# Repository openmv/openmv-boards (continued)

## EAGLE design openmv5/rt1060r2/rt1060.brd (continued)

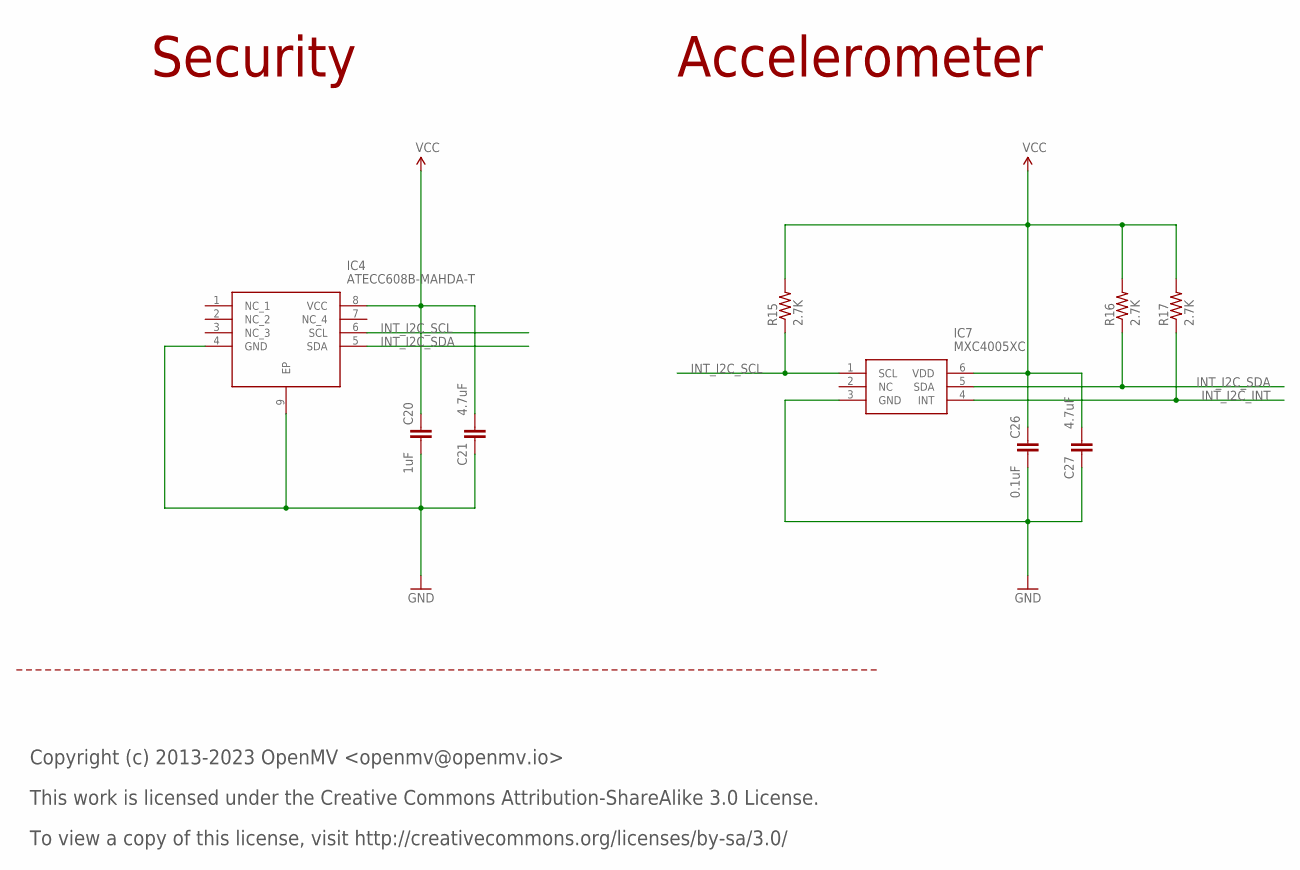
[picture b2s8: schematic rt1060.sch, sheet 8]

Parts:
C20: 1uF; 0402; MPN C0402C104Z4VAC
C21, C27: 4.7uF; 0402-CAP; MPN JMK105BBJ475MV-F
C26: 0.1uF; 0402; MPN C0402C104Z4VAC
IC4: ATECC608B-MAHDA-T; SON50P300X200X60-9N; MPN ATECC608B-MAHDA-T
IC7: MXC4005XC; MPN MXC4005XC
R15, R16, R17: 2.7K; 0402-RES; MPN AC0402JR-072K7L

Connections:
GND: C20.2, C21.1, C26.2, C27.1, IC4.4 (GND), IC4.9 (EP), IC7.3 (GND); also elsewhere on the board
INT_I2C_INT: IC7.4 (INT), R17.1; also elsewhere on the board
INT_I2C_SCL: IC4.6 (SCL), IC7.1 (SCL), R15.1; also elsewhere on the board
INT_I2C_SDA: IC4.5 (SDA), IC7.5 (SDA), R16.1; also elsewhere on the board
VCC: C20.1, C21.2, C26.1, C27.2, IC4.8 (VCC), IC7.6 (VDD), R15.2, R16.2, R17.2; also elsewhere on the board

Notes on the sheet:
Copyright (c) 2013-2023 OpenMV <openmv@openmv.io>
This work is licensed under the Creative Commons Attribution-ShareAlike 3.0 License.
To view a copy of this license, visit http://creativecommons.org/licenses/by-sa/3.0/
Security
Accelerometer

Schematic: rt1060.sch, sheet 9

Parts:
C35: 4.7uF; 0402-CAP; MPN JMK105BBJ475MV-F
C36: 0.1uF; 0402; MPN C0402C104Z4VAC
C37: 22uF; 0805; MPN CL21A226MQQNNNE
D6, D9: CPDQT5V0HE-HF; CPDQT5V0HEHF; MPN CPDQT5V0HE-HF
FL3: EMIF06-1005M12; SON40P150X250X65-13N; MPN EMIF06-1005M12
J5: USD-1040310811; 1040310811; MPN 104031-0811
R50, R51, R52, R53, R54, R55: 100K; 0402; MPN AC0402FR-07100KL

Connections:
GND: C35.1, C36.2, C37.2, D6.2, D9.2, FL3.13 (EP), J5.CD$2 (CD_POL), J5.G$1 (SHD), J5.G$2 (SHD), J5.G$3 (SHD), J5.G$4 (SHD), J5.P$6 (VSS); also elsewhere on the board
SD_CD: D9.1, J5.CD$1 (CD), R50.1; also elsewhere on the board
SD_CLK: FL3.4 (INPUT_4); also elsewhere on the board
SD_CLK_INT: FL3.9 (OUTPUT_4), J5.P$5 (CLK)
SD_CMD: FL3.3 (INPUT_3), R53.1; also elsewhere on the board
SD_CMD_INT: FL3.10 (OUTPUT_3), J5.P$3 (CMD)
SD_DAT0: FL3.5 (INPUT_5), R52.1; also elsewhere on the board
SD_DAT0_INT: FL3.8 (OUTPUT_5), J5.P$7 (DAT0)
SD_DAT1: FL3.6 (INPUT_6), R51.1; also elsewhere on the board
SD_DAT1_INT: FL3.7 (OUTPUT_6), J5.P$8 (DAT1)
SD_DAT2: FL3.1 (INPUT_1), R55.1; also elsewhere on the board
SD_DAT2_INT: FL3.12 (OUTPUT_1), J5.P$1 (DAT2)
SD_DAT3: FL3.2 (INPUT_2), R54.1; also elsewhere on the board
SD_DAT3_INT: FL3.11 (OUTPUT_2), J5.P$2 (DAT3/CD)
VCC: C35.2, C36.1, C37.1, D6.1, J5.P$4 (VDD), R50.2, R51.2, R52.2, R53.2, R54.2, R55.2; also elsewhere on the board

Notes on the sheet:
Copyright (c) 2013-2023 OpenMV <openmv@openmv.io>
This work is licensed under the Creative Commons Attribution-ShareAlike 3.0 License.
To view a copy of this license, visit http://creativecommons.org/licenses/by-sa/3.0/
SD CARD

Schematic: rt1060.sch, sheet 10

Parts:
C32, C51: 22uF; 0805; MPN CL21A226MQQNNNE
C33, C39, C40, C42, C44, C52: 4.7uF; 0402-CAP; MPN JMK105BBJ475MV-F
J4: DF12-36-DS; MPN DF12NB(3.0)-36DS-0.5V(51)
L4: 100; C0402; MPN MFBM1V1005-101-R
Q4, Q5: 2N7002KW_R1_00001; SOT65P210X110-3N; MPN 2N7002KW_R1_00001
R24, R25, R28: 100K; 0402-RES; MPN AC0402FR-07100KL
R26: 1K; 0402-RES; MPN CRCW04021K00FKEDC
R27, R29: 10K; 0402-RES; MPN AC0402FR-1310KL
R30, R31: 4.7K; 0402-RES; MPN AC0402FR-074K7L

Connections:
DCMI_CLK: J4.12; also elsewhere on the board
DCMI_D0: J4.31; also elsewhere on the board
DCMI_D1: J4.29; also elsewhere on the board
DCMI_D2: J4.35; also elsewhere on the board
DCMI_D3: J4.28; also elsewhere on the board
DCMI_D4: J4.26; also elsewhere on the board
DCMI_D5: J4.33; also elsewhere on the board
DCMI_D6: J4.24; also elsewhere on the board
DCMI_D7: J4.22; also elsewhere on the board
DCMI_FSIN: J4.23, Q5.3 (D), R28.1
DCMI_HSYNC: J4.18; also elsewhere on the board
DCMI_MISO: J4.15; also elsewhere on the board
DCMI_MOSI: J4.17; also elsewhere on the board
DCMI_PCLK: J4.14; also elsewhere on the board
DCMI_PWDN: J4.25, R29.1; also elsewhere on the board
DCMI_RST: J4.21, R27.1; also elsewhere on the board
DCMI_SCL: J4.32, R30.1; also elsewhere on the board
DCMI_SCLK: J4.13; also elsewhere on the board
DCMI_SDA: J4.34, R31.1; also elsewhere on the board
DCMI_SSEL: J4.11, R24.1; also elsewhere on the board
DCMI_VSYNC: J4.16; also elsewhere on the board
GND: C32.2, C33.1, C39.1, C40.1, C42.1, C44.1, C51.2, C52.1, J4.5, J4.19, J4.27, R27.2; also elsewhere on the board
P10_PWM: Q4.3 (D), R26.1; also elsewhere on the board
PWM_FSIN: Q4.2 (S), Q5.2 (S), R25.1; also elsewhere on the board
VCC: C32.1, C33.2, C39.2, C40.2, C42.2, C44.2, J4.2, J4.10, J4.20, J4.30, J4.36, L4.2, Q4.1 (G), Q5.1 (G), R24.2, R25.2, R26.2, R28.2, R29.2, R30.2, R31.2; also elsewhere on the board
VDDA: C51.1, C52.2, J4.4, L4.1

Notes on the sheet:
Copyright (c) 2013-2023 OpenMV <openmv@openmv.io>
This work is licensed under the Creative Commons Attribution-ShareAlike 3.0 License.
To view a copy of this license, visit http://creativecommons.org/licenses/by-sa/3.0/
IMAGE SENSOR CONNECTOR

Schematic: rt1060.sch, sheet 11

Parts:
D3: UHD1110-FKA-CL1A13R3Q1BBQFMF3; LED_UHD1110-FKA-CL1A13R3Q1BBQFMF3; MPN UHD1110-FKA-CL1A13r3q1BBQFMF3
D4, D5, D7, D8: CPDQT5V0HE-HF; CPDQT5V0HEHF; MPN CPDQT5V0HE-HF
FL2, FL4: EMIF06-1005M12; SON40P150X250X65-13N; MPN EMIF06-1005M12
J2, J3, J6: DNP; 1X08
R19, R20, R21: 220; 0402-RES; MPN CRGCQ0402F220R
R56, R57, R58: 10K; 0402; MPN AC0402FR-1310KL

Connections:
GND: D4.2, D5.2, D7.2, D8.2, FL2.13 (EP), FL4.13 (EP), J3.1, J6.1; also elsewhere on the board
LED_B: R19.1, R56.1; also elsewhere on the board
LED_B_INT: D3.1 (BLUE), R19.2
LED_G: R20.1, R57.1; also elsewhere on the board
LED_G_INT: D3.2 (GREEN), R20.2
LED_R: R21.1, R58.1; also elsewhere on the board
LED_R_INT: D3.3 (RED), R21.2
MDI_LED: J3.8; also elsewhere on the board
MDI_RX_N: J3.7; also elsewhere on the board
MDI_RX_P: J3.6; also elsewhere on the board
MDI_TX_N: J3.5; also elsewhere on the board
MDI_TX_P: J3.4; also elsewhere on the board
P0_MOSI: FL2.1 (INPUT_1); also elsewhere on the board
P0_MOSI_INT: FL2.12 (OUTPUT_1), J2.8
P1_MISO: FL2.2 (INPUT_2); also elsewhere on the board
P1_MISO_INT: FL2.11 (OUTPUT_2), J2.7
P2_SCLK: FL2.3 (INPUT_3); also elsewhere on the board
P2_SCLK_INT: FL2.10 (OUTPUT_3), J2.6
P3_NSS: FL2.4 (INPUT_4); also elsewhere on the board
P3_NSS_INT: FL2.9 (OUTPUT_4), J2.5
P4_SCL: FL2.5 (INPUT_5); also elsewhere on the board
P4_SCL_INT: FL2.8 (OUTPUT_5), J2.4
P5_SDA: FL2.6 (INPUT_6); also elsewhere on the board
P5_SDA_INT: FL2.7 (OUTPUT_6), J2.3
P6_ADC: FL4.1 (INPUT_1); also elsewhere on the board
P6_ADC_INT: FL4.12 (OUTPUT_1), J2.2
P7_PWM: FL4.2 (INPUT_2); also elsewhere on the board
P7_PWM_INT: FL4.11 (OUTPUT_2), J6.3
P8_PWM: FL4.3 (INPUT_3); also elsewhere on the board
P8_PWM_INT: FL4.10 (OUTPUT_3), J6.4
P9_PWM: FL4.4 (INPUT_4); also elsewhere on the board
P9_PWM_INT: FL4.9 (OUTPUT_4), J6.5
P10_PWM: FL4.5 (INPUT_5); also elsewhere on the board
P10_PWM_INT: FL4.8 (OUTPUT_5), J6.6
P11_WAKEUP: FL4.6 (INPUT_6); also elsewhere on the board
P11_WAKEUP_INT: FL4.7 (OUTPUT_6), J6.7
P12_RST_N_EXT: J6.8; also elsewhere on the board
PMIC_ONOFF: D8.1, J3.3; also elsewhere on the board
RAW: D5.1, J3.2; also elsewhere on the board
VCC: D3.4 (ANODE), D4.1, J2.1, R56.2, R57.2, R58.2; also elsewhere on the board
VIN: D7.1, J6.2; also elsewhere on the board

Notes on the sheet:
Copyright (c) 2013-2023 OpenMV <openmv@openmv.io>
This work is licensed under the Creative Commons Attribution-ShareAlike 3.0 License.
To view a copy of this license, visit http://creativecommons.org/licenses/by-sa/3.0/
I/O HEADERS
RGB LED

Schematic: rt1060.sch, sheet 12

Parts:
D10: CPDQT5V0HE-HF; CPDQT5V0HEHF; MPN CPDQT5V0HE-HF
FL5: EMIF06-1005M12; SON40P150X250X65-13N; MPN EMIF06-1005M12
J8: 3221-10-0300-00; CNC_3221-10-0300-00; MPN 3221-10-0300-00
R37: 10K; 0402-RES; MPN AC0402FR-1310KL

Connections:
BT_REG_ON: R37.1; also elsewhere on the board
GND: D10.2, FL5.13 (EP), J8.3, J8.5, R37.2; also elsewhere on the board
JTAG_TCK: FL5.4 (INPUT_4); also elsewhere on the board
JTAG_TCK_INT: FL5.9 (OUTPUT_4), J8.4
JTAG_TDI: FL5.2 (INPUT_2); also elsewhere on the board
JTAG_TDI_INT: FL5.11 (OUTPUT_2), J8.8
JTAG_TDO: FL5.3 (INPUT_3); also elsewhere on the board
JTAG_TDO_INT: FL5.10 (OUTPUT_3), J8.6
JTAG_TMS: FL5.5 (INPUT_5); also elsewhere on the board
JTAG_TMS_INT: FL5.8 (OUTPUT_5), J8.2
JTAG_TRSTB: FL5.6 (INPUT_6); also elsewhere on the board
JTAG_TRSTB_INT: FL5.7 (OUTPUT_6), J8.9
P12_RST_N: FL5.1 (INPUT_1); also elsewhere on the board
P12_RST_N_EXT: FL5.12 (OUTPUT_1), J8.10; also elsewhere on the board
VCC: D10.1, J8.1; also elsewhere on the board

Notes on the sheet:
Copyright (c) 2013-2023 OpenMV <openmv@openmv.io>
This work is licensed under the Creative Commons Attribution-ShareAlike 3.0 License.
To view a copy of this license, visit http://creativecommons.org/licenses/by-sa/3.0/
JTAG

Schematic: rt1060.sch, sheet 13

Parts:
C65, C81, C83, C90: 4.7uF; 0402-CAP; MPN JMK105BBJ475MV-F
C82, C84, C89: 0.1uF; 0402; MPN C0402C104Z4VAC
C85, C96: 22uF; 0805; MPN CL21A226MQQNNNE
FD1, FD2, FD3, FD4, FD5, FD6, FD7, FD8: FIDUCIAL1X2; FIDUCIAL-1X2
H1, H2: MOUNT-PAD-ROUND2.8; 2,8-PAD
IC9: KSZ8081RNDCA-TR; QFN50P400X400X90-25N; MPN KSZ8081RNDCA-TR
L8: 100; C0402; MPN MFBM1V1005-101-R
M1, M2: 9774030151R; MPN 9774030151R
R34: 100K; 0402-RES; MPN AC0402FR-07100KL
R35: 220; 0402-RES; MPN CRGCQ0402F220R
R36, R39: 1K; 0402-RES; MPN CRCW04021K00FKEDC
R38: 6.49K; 0402-RES; MPN CR0402-FX-6491GLF

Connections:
ETH_INT: IC9.18 (INTRP), R36.1; also elsewhere on the board
ETH_LED: IC9.23 (LED0_/_ANEN_SPEED), R35.1
ETH_MDC: IC9.11 (MDC); also elsewhere on the board
ETH_MDIO: IC9.10 (MDIO), R39.1; also elsewhere on the board
ETH_RST: C65.2, IC9.24 (RST#), R34.1; also elsewhere on the board
ETH_RXD0: IC9.13 (RXD0); also elsewhere on the board
ETH_RXD1: IC9.12 (RXD1); also elsewhere on the board
ETH_RXDV: IC9.15 (CRS_DV/_PHYAD[1:0]); also elsewhere on the board
ETH_RXERR: IC9.17 (RXER); also elsewhere on the board
ETH_TXCLK: IC9.8 (XI); also elsewhere on the board
ETH_TXD0: IC9.20 (TXD0); also elsewhere on the board
ETH_TXD1: IC9.21 (TXD1); also elsewhere on the board
ETH_TXEN: IC9.19 (TXEN); also elsewhere on the board
ETH_VDDA_3.3: C81.2, C82.1, C85.1, IC9.2 (VDDA_3.3), L8.1
ETH_VDD_1.2: C83.2, C84.1, IC9.1 (VDD_1.2)
GND: C65.1, C81.1, C82.2, C83.1, C84.2, C85.2, C89.2, C90.1, C96.2, IC9.22 (GND_1), IC9.25 (GND_2), R38.2; also elsewhere on the board
MDI_LED: R35.2; also elsewhere on the board
MDI_RX_N: IC9.3 (RXM); also elsewhere on the board
MDI_RX_P: IC9.4 (RXP); also elsewhere on the board
MDI_TX_N: IC9.5 (TXM); also elsewhere on the board
MDI_TX_P: IC9.6 (TXP); also elsewhere on the board
REXT: IC9.9 (REXT), R38.1
VCC: C89.1, C90.2, C96.1, IC9.14 (VDDIO), L8.2, R34.2, R36.2, R39.2; also elsewhere on the board

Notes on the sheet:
Copyright (c) 2013-2023 OpenMV <openmv@openmv.io>
This work is licensed under the Creative Commons Attribution-ShareAlike 3.0 License.
To view a copy of this license, visit http://creativecommons.org/licenses/by-sa/3.0/
Ethernet
Mechanical

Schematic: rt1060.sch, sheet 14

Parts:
ANT1: AMCA31-2R450G-S1F-T3; ANTC3216X140N; MPN AMCA31-2R450G-S1F-T3
C74, C75, C76, C111: 0.1uF; 0402; MPN C0402C104Z4VAC
C77: GRM0335C1H1R5BA01D; CAPC0603X33N; MPN GRM0335C1H1R5BA01D
C78: DNP; CAPC0603X33N; MPN GRM0335C1H1R5BA01D
C91, C92, C93: 4.7uF; 0402-CAP; MPN JMK105BBJ475MV-F
J7: DNP; 23370191; MPN 2337019-1
L7: 3.9NH; 0402; MPN L-07C3N9SV6T
L9: MAKK2016T2R2M; INDC2016X100N; MPN MAKK2016T2R2M
R43, R44: 10K; 0402; MPN AC0402FR-1310KL
R45, R46, R47, R48, R49: 100K; 0402; MPN AC0402FR-07100KL
U3: LBEE5KL1DX-883; XCVR_LBEE5KL1DX-TEMP; MPN LBEE5KL1DX-883
Y3: ECS-327MVATX-3-CN-TR3; ECS327MVATX3CNTR3; MPN ECS-327MVATX-3-CN-TR3

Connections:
ANT: C77.1, J7.1 (SIGNAL), L7.2, U3.41 (ANT)
BT_D_WAKE: U3.39 (BT_DEV_WAKE); also elsewhere on the board
BT_H_WAKE: R44.1, U3.38 (BT_HOST_WAKE); also elsewhere on the board
BT_REG_ON: U3.14 (BT_REG_ON); also elsewhere on the board
BT_UART_CTS: U3.5 (!BT_UART_RTS_N); also elsewhere on the board
BT_UART_RTS: U3.4 (!BT_UART_CTS_N); also elsewhere on the board
BT_UART_RX: U3.3 (BT_UART_TXD); also elsewhere on the board
BT_UART_TX: U3.2 (BT_UART_RXD); also elsewhere on the board
FEED: ANT1.1 (FEED), C78.1, L7.1
GND: C74.2, C75.2, C76.2, C77.2, C78.2, C91.1, C92.1, C93.1, C111.2, J7.2 (GND_1), J7.3 (GND_2), U3.1 (GND), U3.12 (GND), U3.19 (GND), U3.21 (GND), U3.29 (GND), U3.32 (GND_(SR_PVSS)), U3.33 (GND_(SR_PVSS)), U3.35 (GND), U3.40 (GND), U3.42 (GND), U3.43 (GND), U3.44 (GND), U3.45 (GND), U3.46 (GND), Y3.2 (GND); also elsewhere on the board
LPO_IN: U3.37 (LPO_IN_(32KHZ)), Y3.3 (OUTPUT)
SR_VLX: L9.1, U3.34 (SR_VLX)
VCC: C75.1, C76.1, C92.2, C93.2, C111.1, R43.2, R44.2, R45.2, R46.2, R47.2, R48.2, R49.2, U3.30 (VBAT), U3.36 (VIO), Y3.1 (TRI-STATE), Y3.4 (VDD); also elsewhere on the board
VIN_LDO: C74.1, C91.2, L9.2, U3.31 (VIN_LDO)
WIFI_CLK: U3.20 (SDIO_CLK); also elsewhere on the board
WIFI_CMD: R49.1, U3.22 (SDIO_CMD); also elsewhere on the board
WIFI_D0: R48.1, U3.24 (SDIO_DATA_0); also elsewhere on the board
WIFI_D1: R47.1, U3.26 (SDIO_DATA_1); also elsewhere on the board
WIFI_D2: R46.1, U3.23 (SDIO_DATA_2); also elsewhere on the board
WIFI_D3: R45.1, U3.25 (SDIO_DATA_3); also elsewhere on the board
WL_H_WAKE: R43.1, U3.27 (WL_GPIO_0_HOST_WAKE); also elsewhere on the board
WL_REG_ON: U3.28 (WL_REG_ON); also elsewhere on the board

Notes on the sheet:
Copyright (c) 2013-2023 OpenMV <openmv@openmv.io>
This work is licensed under the Creative Commons Attribution-ShareAlike 3.0 License.
To view a copy of this license, visit http://creativecommons.org/licenses/by-sa/3.0/
WiFi/Bluetooth

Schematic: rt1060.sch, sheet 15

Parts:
C34, C38, C43, C45, C47, C48, C50, C53, C54, C55, C56, C59, C62, C63, C66, C68, C69, C70, C71, C86, C87, C88, C94, C97, C98, C99, C100, C102, C103, C107, C109: 0.22uF; C0201; MPN GRM033R60J224ME15D
C41, C46, C57, C60, C64, C67, C72, C95, C101, C104, C108: 4.7uF; 0402-CAP; MPN JMK105BBJ475MV-F
C49, C58, C61, C73: 22uF; 0805; MPN CL21A226MQQNNNE
C79, C80: 18pF; C0201; MPN GRM0335C1E180JA01D
C105, C106: 4.7pF; C0201; MPN GRM0335C1E4R7CA01D
IC8: MIMXRT1052DVL6B; BGA196C65P14X14_1000X1000X143; MPN MIMXRT1052DVL6B
L5: MAKK2016T4R7M; INDC2016X100N; MPN MAKK2016T4R7M
L6: 100; C0402; MPN MFBM1V1005-101-R
R32: 30K; 0402-RES; MPN 0402WGF3002TCE
R33, R42: 10K; 0402-RES; MPN AC0402FR-1310KL
R40: 2.2M; 0402-RES; MPN RC0402FR-072M2L
S1: KMS231GLFS; MPN KMS231GLFS
Y1: SC32S-7PF20PPM; XTAL_ABS07-32.768KHZ-7-T; MPN SC32S-7PF20PPM
Y2: XRCGB24M000F3M00R0; MPN XRCGB24M000F3M00R0

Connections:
BT_D_WAKE: IC8.L5 (GPIO_SD_B1_00); also elsewhere on the board
BT_H_WAKE: IC8.H14 (GPIO_AD_B0_14); also elsewhere on the board
BT_REG_ON: IC8.F13 (GPIO_AD_B0_08); also elsewhere on the board
BT_UART_CTS: IC8.L12 (GPIO_AD_B1_04); also elsewhere on the board
BT_UART_RTS: IC8.K12 (GPIO_AD_B1_05); also elsewhere on the board
BT_UART_RX: IC8.C9 (GPIO_B0_09); also elsewhere on the board
BT_UART_TX: IC8.B9 (GPIO_B0_08); also elsewhere on the board
DCDC_LP: IC8.M1 (DCDC_LP_1), IC8.M2 (DCDC_LP_2), L5.2
DCDC_PSWITCH: C62.1, IC8.K3 (DCDC_PSWITCH), R32.1
DCMI_CLK: IC8.B14 (GPIO_B1_15); also elsewhere on the board
DCMI_D0: IC8.J14 (GPIO_AD_B1_15); also elsewhere on the board
DCMI_D1: IC8.G12 (GPIO_AD_B1_14); also elsewhere on the board
DCMI_D2: IC8.H11 (GPIO_AD_B1_13); also elsewhere on the board
DCMI_D3: IC8.H12 (GPIO_AD_B1_12); also elsewhere on the board
DCMI_D4: IC8.J13 (GPIO_AD_B1_11); also elsewhere on the board
DCMI_D5: IC8.L13 (GPIO_AD_B1_10); also elsewhere on the board
DCMI_D6: IC8.G14 (GPIO_AD_B0_05); also elsewhere on the board
DCMI_D7: IC8.F11 (GPIO_AD_B0_04), S1.1 (NO_1), S1.5 (NO_2); also elsewhere on the board
DCMI_HSYNC: IC8.L10 (GPIO_AD_B0_15); also elsewhere on the board
DCMI_MISO: IC8.E7 (GPIO_B0_01); also elsewhere on the board
DCMI_MOSI: IC8.E8 (GPIO_B0_02); also elsewhere on the board
DCMI_PCLK: IC8.D13 (GPIO_B1_12); also elsewhere on the board
DCMI_PWDN: IC8.C11 (GPIO_B1_02); also elsewhere on the board
DCMI_RST: IC8.B11 (GPIO_B1_01); also elsewhere on the board
DCMI_SCL: IC8.J11 (GPIO_AD_B1_00); also elsewhere on the board
DCMI_SCLK: IC8.D8 (GPIO_B0_03); also elsewhere on the board
DCMI_SDA: IC8.K11 (GPIO_AD_B1_01); also elsewhere on the board
DCMI_SSEL: IC8.D7 (GPIO_B0_00); also elsewhere on the board
DCMI_VSYNC: IC8.D14 (GPIO_B1_13); also elsewhere on the board
ETH_INT: IC8.C10 (GPIO_B0_12); also elsewhere on the board
ETH_MDC: IC8.A7 (GPIO_EMC_40); also elsewhere on the board
ETH_MDIO: IC8.C7 (GPIO_EMC_41); also elsewhere on the board
ETH_RST: IC8.D10 (GPIO_B0_13); also elsewhere on the board
ETH_RXD0: IC8.E12 (GPIO_B1_04); also elsewhere on the board
ETH_RXD1: IC8.D12 (GPIO_B1_05); also elsewhere on the board
ETH_RXDV: IC8.C12 (GPIO_B1_06); also elsewhere on the board
ETH_RXERR: IC8.C13 (GPIO_B1_11); also elsewhere on the board
ETH_TXCLK: IC8.B13 (GPIO_B1_10); also elsewhere on the board
ETH_TXD0: IC8.B12 (GPIO_B1_07); also elsewhere on the board
ETH_TXD1: IC8.A12 (GPIO_B1_08); also elsewhere on the board
ETH_TXEN: IC8.A13 (GPIO_B1_09); also elsewhere on the board
GND: C34.2, C38.2, C41.1, C43.2, C45.2, C46.1, C47.2, C48.2, C49.1, C50.2, C53.2, C54.2, C55.2, C56.2, C57.1, C58.1, C59.2, C60.1, C61.1, C62.2, C63.2, C64.2, C66.1, C67.2, C68.1, C69.2, C70.2, C71.2, C72.1, C73.1, C79.2, C80.2, C86.1, C87.1, C88.2, C94.1, C95.1, C97.1, C98.1, C99.1, C100.1, C101.1, C102.2, C103.1, C104.1, C105.2, C106.2, C107.2, C108.1, C109.2, IC8.A1 (VSS_1), IC8.A14 (VSS_2), IC8.B5 (VSS_3), IC8.B10 (VSS_4), IC8.E2 (VSS_5), IC8.E13 (VSS_6), IC8.G7 (VSS_7), IC8.G8 (VSS_8), IC8.H7 (VSS_9), IC8.H8 (VSS_10), IC8.J7 (VSS_11), IC8.J8 (VSS_12), IC8.K2 (VSS_13), IC8.K6 (TEST_MODE), IC8.K9 (NGND_KEL0), IC8.K13 (VSS_14), IC8.L9 (VSS_15), IC8.N1 (DCDC_GND_1), IC8.N2 (DCDC_GND_2), IC8.N5 (VSS_16), IC8.N8 (VSS_17), IC8.P1 (VSS_18), IC8.P14 (VSS_19), R40.2, Y2.2 (NC_1), Y2.4 (NC_2); also elsewhere on the board
INT_I2C_INT: IC8.D11 (GPIO_B1_03); also elsewhere on the board
INT_I2C_SCL: IC8.C8 (GPIO_B0_04); also elsewhere on the board
INT_I2C_SDA: IC8.B8 (GPIO_B0_05); also elsewhere on the board
JTAG_TCK: IC8.F12 (GPIO_AD_B0_07); also elsewhere on the board
JTAG_TDI: IC8.F14 (GPIO_AD_B0_09); also elsewhere on the board
JTAG_TDO: IC8.G13 (GPIO_AD_B0_10); also elsewhere on the board
JTAG_TMS: IC8.E14 (GPIO_AD_B0_06); also elsewhere on the board
JTAG_TRSTB: IC8.G10 (GPIO_AD_B0_11); also elsewhere on the board
LED_B: IC8.C14 (GPIO_B1_14); also elsewhere on the board
LED_G: IC8.A10 (GPIO_B0_11); also elsewhere on the board
LED_R: IC8.D9 (GPIO_B0_10); also elsewhere on the board
NVCC_PLL: C104.2, C107.1, IC8.P10 (NVCC_PLL)
ONOFF: IC8.M6 (ONOFF); also elsewhere on the board
ON_BATTERY: IC8.P2 (GPIO_SD_B1_04); also elsewhere on the board
P0_MOSI: IC8.H10 (GPIO_AD_B0_01); also elsewhere on the board
P1_MISO: IC8.M11 (GPIO_AD_B0_02); also elsewhere on the board
P2_SCLK: IC8.M14 (GPIO_AD_B0_00); also elsewhere on the board
P3_NSS: IC8.G11 (GPIO_AD_B0_03); also elsewhere on the board
P4_SCL: IC8.K14 (GPIO_AD_B0_12); also elsewhere on the board
P5_SDA: IC8.L14 (GPIO_AD_B0_13); also elsewhere on the board
P6_ADC: IC8.M12 (GPIO_AD_B1_03); also elsewhere on the board
P7_PWM: IC8.A8 (GPIO_B0_06); also elsewhere on the board
P8_PWM: IC8.A9 (GPIO_B0_07); also elsewhere on the board
P9_PWM: IC8.A11 (GPIO_B1_00); also elsewhere on the board
P12_RST_N: C63.1, IC8.M7 (POR_B), R33.2; also elsewhere on the board
PMIC_ON_REQ: IC8.K7 (PMIC_ON_REQ); also elsewhere on the board
PWM_FSIN: IC8.M5 (GPIO_SD_B1_01); also elsewhere on the board
P_FLASH_CE: IC8.L3 (GPIO_SD_B1_06); also elsewhere on the board
P_FLASH_IO0: IC8.P3 (GPIO_SD_B1_08); also elsewhere on the board
P_FLASH_IO1: IC8.N4 (GPIO_SD_B1_09); also elsewhere on the board
P_FLASH_IO2: IC8.P4 (GPIO_SD_B1_10); also elsewhere on the board
P_FLASH_IO3: IC8.P5 (GPIO_SD_B1_11); also elsewhere on the board
P_FLASH_SCK: IC8.L4 (GPIO_SD_B1_07); also elsewhere on the board
RTC_XTALI: C80.1, IC8.N9 (RTC_XTALI), Y1.2
RTC_XTALO: C79.1, IC8.P9 (RTC_XTALO), Y1.1
SBL_BOOT: R42.2, S1.2 (COM_1), S1.3 (COM_2), S1.4 (COM_3)
SDRAM_A0: IC8.C2 (GPIO_EMC_09); also elsewhere on the board
SDRAM_A1: IC8.G1 (GPIO_EMC_10); also elsewhere on the board
SDRAM_A2: IC8.G3 (GPIO_EMC_11); also elsewhere on the board
SDRAM_A3: IC8.H1 (GPIO_EMC_12); also elsewhere on the board
SDRAM_A4: IC8.A6 (GPIO_EMC_13); also elsewhere on the board
SDRAM_A5: IC8.B6 (GPIO_EMC_14); also elsewhere on the board
SDRAM_A6: IC8.B1 (GPIO_EMC_15); also elsewhere on the board
SDRAM_A7: IC8.A5 (GPIO_EMC_16); also elsewhere on the board
SDRAM_A8: IC8.A4 (GPIO_EMC_17); also elsewhere on the board
SDRAM_A9: IC8.B2 (GPIO_EMC_18); also elsewhere on the board
SDRAM_A10: IC8.G2 (GPIO_EMC_23); also elsewhere on the board
SDRAM_A11: IC8.B4 (GPIO_EMC_19); also elsewhere on the board
SDRAM_A12: IC8.A3 (GPIO_EMC_20); also elsewhere on the board
SDRAM_BA0: IC8.C1 (GPIO_EMC_21); also elsewhere on the board
SDRAM_BA1: IC8.F1 (GPIO_EMC_22); also elsewhere on the board
SDRAM_CAS: IC8.D3 (GPIO_EMC_24); also elsewhere on the board
SDRAM_CKE: IC8.A2 (GPIO_EMC_27); also elsewhere on the board
SDRAM_CLK: IC8.B3 (GPIO_EMC_26); also elsewhere on the board
SDRAM_CS: IC8.E1 (GPIO_EMC_29); also elsewhere on the board
SDRAM_DQ0: IC8.E3 (GPIO_EMC_00); also elsewhere on the board
SDRAM_DQ1: IC8.F3 (GPIO_EMC_01); also elsewhere on the board
SDRAM_DQ2: IC8.F4 (GPIO_EMC_02); also elsewhere on the board
SDRAM_DQ3: IC8.G4 (GPIO_EMC_03); also elsewhere on the board
SDRAM_DQ4: IC8.F2 (GPIO_EMC_04); also elsewhere on the board
SDRAM_DQ5: IC8.G5 (GPIO_EMC_05); also elsewhere on the board
SDRAM_DQ6: IC8.H5 (GPIO_EMC_06); also elsewhere on the board
SDRAM_DQ7: IC8.H4 (GPIO_EMC_07); also elsewhere on the board
SDRAM_DQ8: IC8.C6 (GPIO_EMC_30); also elsewhere on the board
SDRAM_DQ9: IC8.C5 (GPIO_EMC_31); also elsewhere on the board
SDRAM_DQ10: IC8.D5 (GPIO_EMC_32); also elsewhere on the board
SDRAM_DQ11: IC8.C4 (GPIO_EMC_33); also elsewhere on the board
SDRAM_DQ12: IC8.D4 (GPIO_EMC_34); also elsewhere on the board
SDRAM_DQ13: IC8.E5 (GPIO_EMC_35); also elsewhere on the board
SDRAM_DQ14: IC8.C3 (GPIO_EMC_36); also elsewhere on the board
SDRAM_DQ15: IC8.E4 (GPIO_EMC_37); also elsewhere on the board
SDRAM_DQMH: IC8.D6 (GPIO_EMC_38); also elsewhere on the board
SDRAM_DQML: IC8.H3 (GPIO_EMC_08); also elsewhere on the board
SDRAM_RAS: IC8.D2 (GPIO_EMC_25); also elsewhere on the board
SDRAM_WE: IC8.D1 (GPIO_EMC_28); also elsewhere on the board
SD_CD: IC8.L11 (GPIO_AD_B1_02); also elsewhere on the board
SD_CLK: IC8.J3 (GPIO_SD_B0_01); also elsewhere on the board
SD_CMD: IC8.J4 (GPIO_SD_B0_00); also elsewhere on the board
SD_DAT0: IC8.J1 (GPIO_SD_B0_02); also elsewhere on the board
SD_DAT1: IC8.K1 (GPIO_SD_B0_03); also elsewhere on the board
SD_DAT2: IC8.H2 (GPIO_SD_B0_04); also elsewhere on the board
SD_DAT3: IC8.J2 (GPIO_SD_B0_05); also elsewhere on the board
USB_D_N: IC8.M8 (USB_OTG1_DN); also elsewhere on the board
USB_D_P: IC8.L8 (USB_OTG1_DP); also elsewhere on the board
VBUS: C88.1, C95.2, IC8.N6 (USB_OTG1_VBUS); also elsewhere on the board
VCC: C41.2, C43.1, C50.1, C53.1, C54.1, C55.1, C56.1, C57.2, C58.2, C64.1, C66.2, C67.1, C68.2, C86.2, C99.2, C108.2, C109.1, IC8.E6 (NVCC_EMC_1), IC8.E9 (NVCC_GPIO_1), IC8.F5 (NVCC_EMC_2), IC8.F10 (NVCC_GPIO_2), IC8.J6 (NVCC_SD0), IC8.J10 (NVCC_GPIO_3), IC8.K4 (DCDC_IN_Q), IC8.K5 (NVCC_SD1), IC8.L1 (DCDC_IN_1), IC8.L2 (DCDC_IN_2), IC8.P12 (VDD_HIGH_IN), L6.2, R32.2, R33.1, R42.1; also elsewhere on the board
VCC_SOC: C34.1, C38.1, C45.1, C46.2, C47.1, C48.1, C49.2, C87.2, C94.2, C97.2, C98.2, C100.2, C103.2, IC8.F6 (VDD_SOC_IN_1), IC8.F7 (VDD_SOC_IN_2), IC8.F8 (VDD_SOC_IN_3), IC8.F9 (VDD_SOC_IN_4), IC8.G6 (VDD_SOC_IN_5), IC8.G9 (VDD_SOC_IN_6), IC8.H6 (VDD_SOC_IN_7), IC8.H9 (VDD_SOC_IN_8), IC8.J5 (DCDC_SENSE), IC8.J9 (VDD_SOC_IN_9), L5.1
VDDA_ADC_3P3: C59.1, C60.2, C61.2, IC8.N14 (VDDA_ADC_3P3), L6.1
VDD_HIGH_CAP: C101.2, C102.1, IC8.P8 (VDD_HIGH_CAP)
VDD_SNVS: C69.1, IC8.M9 (VDD_SNVS_IN); also elsewhere on the board
VDD_SNVS_CAP: C70.1, IC8.M10 (VDD_SNVS_CAP)
VDD_USB_CAP: C71.1, C72.2, C73.2, IC8.K8 (VDD_USB_CAP)
WAKEUP: IC8.L6 (WAKEUP); also elsewhere on the board
WIFI_CLK: IC8.M13 (GPIO_AD_B1_09); also elsewhere on the board
WIFI_CMD: IC8.H13 (GPIO_AD_B1_08); also elsewhere on the board
WIFI_D0: IC8.M4 (GPIO_SD_B1_03); also elsewhere on the board
WIFI_D1: IC8.M3 (GPIO_SD_B1_02); also elsewhere on the board
WIFI_D2: IC8.J12 (GPIO_AD_B1_06); also elsewhere on the board
WIFI_D3: IC8.K10 (GPIO_AD_B1_07); also elsewhere on the board
WL_H_WAKE: IC8.E11 (GPIO_B0_15); also elsewhere on the board
WL_REG_ON: IC8.E10 (GPIO_B0_14); also elsewhere on the board
XTALI: C106.1, IC8.P11 (XTALI), R40.1, Y2.3 (CRYSTAL_2)
XTALO: C105.1, IC8.N11 (XTALO), Y2.1 (CRYSTAL_1)

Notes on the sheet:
Copyright (c) 2013-2023 OpenMV <openmv@openmv.io>
This work is licensed under the Creative Commons Attribution-ShareAlike 3.0 License.
To view a copy of this license, visit http://creativecommons.org/licenses/by-sa/3.0/
MIMXRT10XX
SDRAM_DQS
P_FLASH_DQS

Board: 8 copper layers, 239 parts (169 on the bottom side), 215 nets, no tracks yet.

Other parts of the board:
U$1: WEEE
U$2: ROHS
U$3: OMV-LOGO
U$4: OMV-LOGO-SMALL

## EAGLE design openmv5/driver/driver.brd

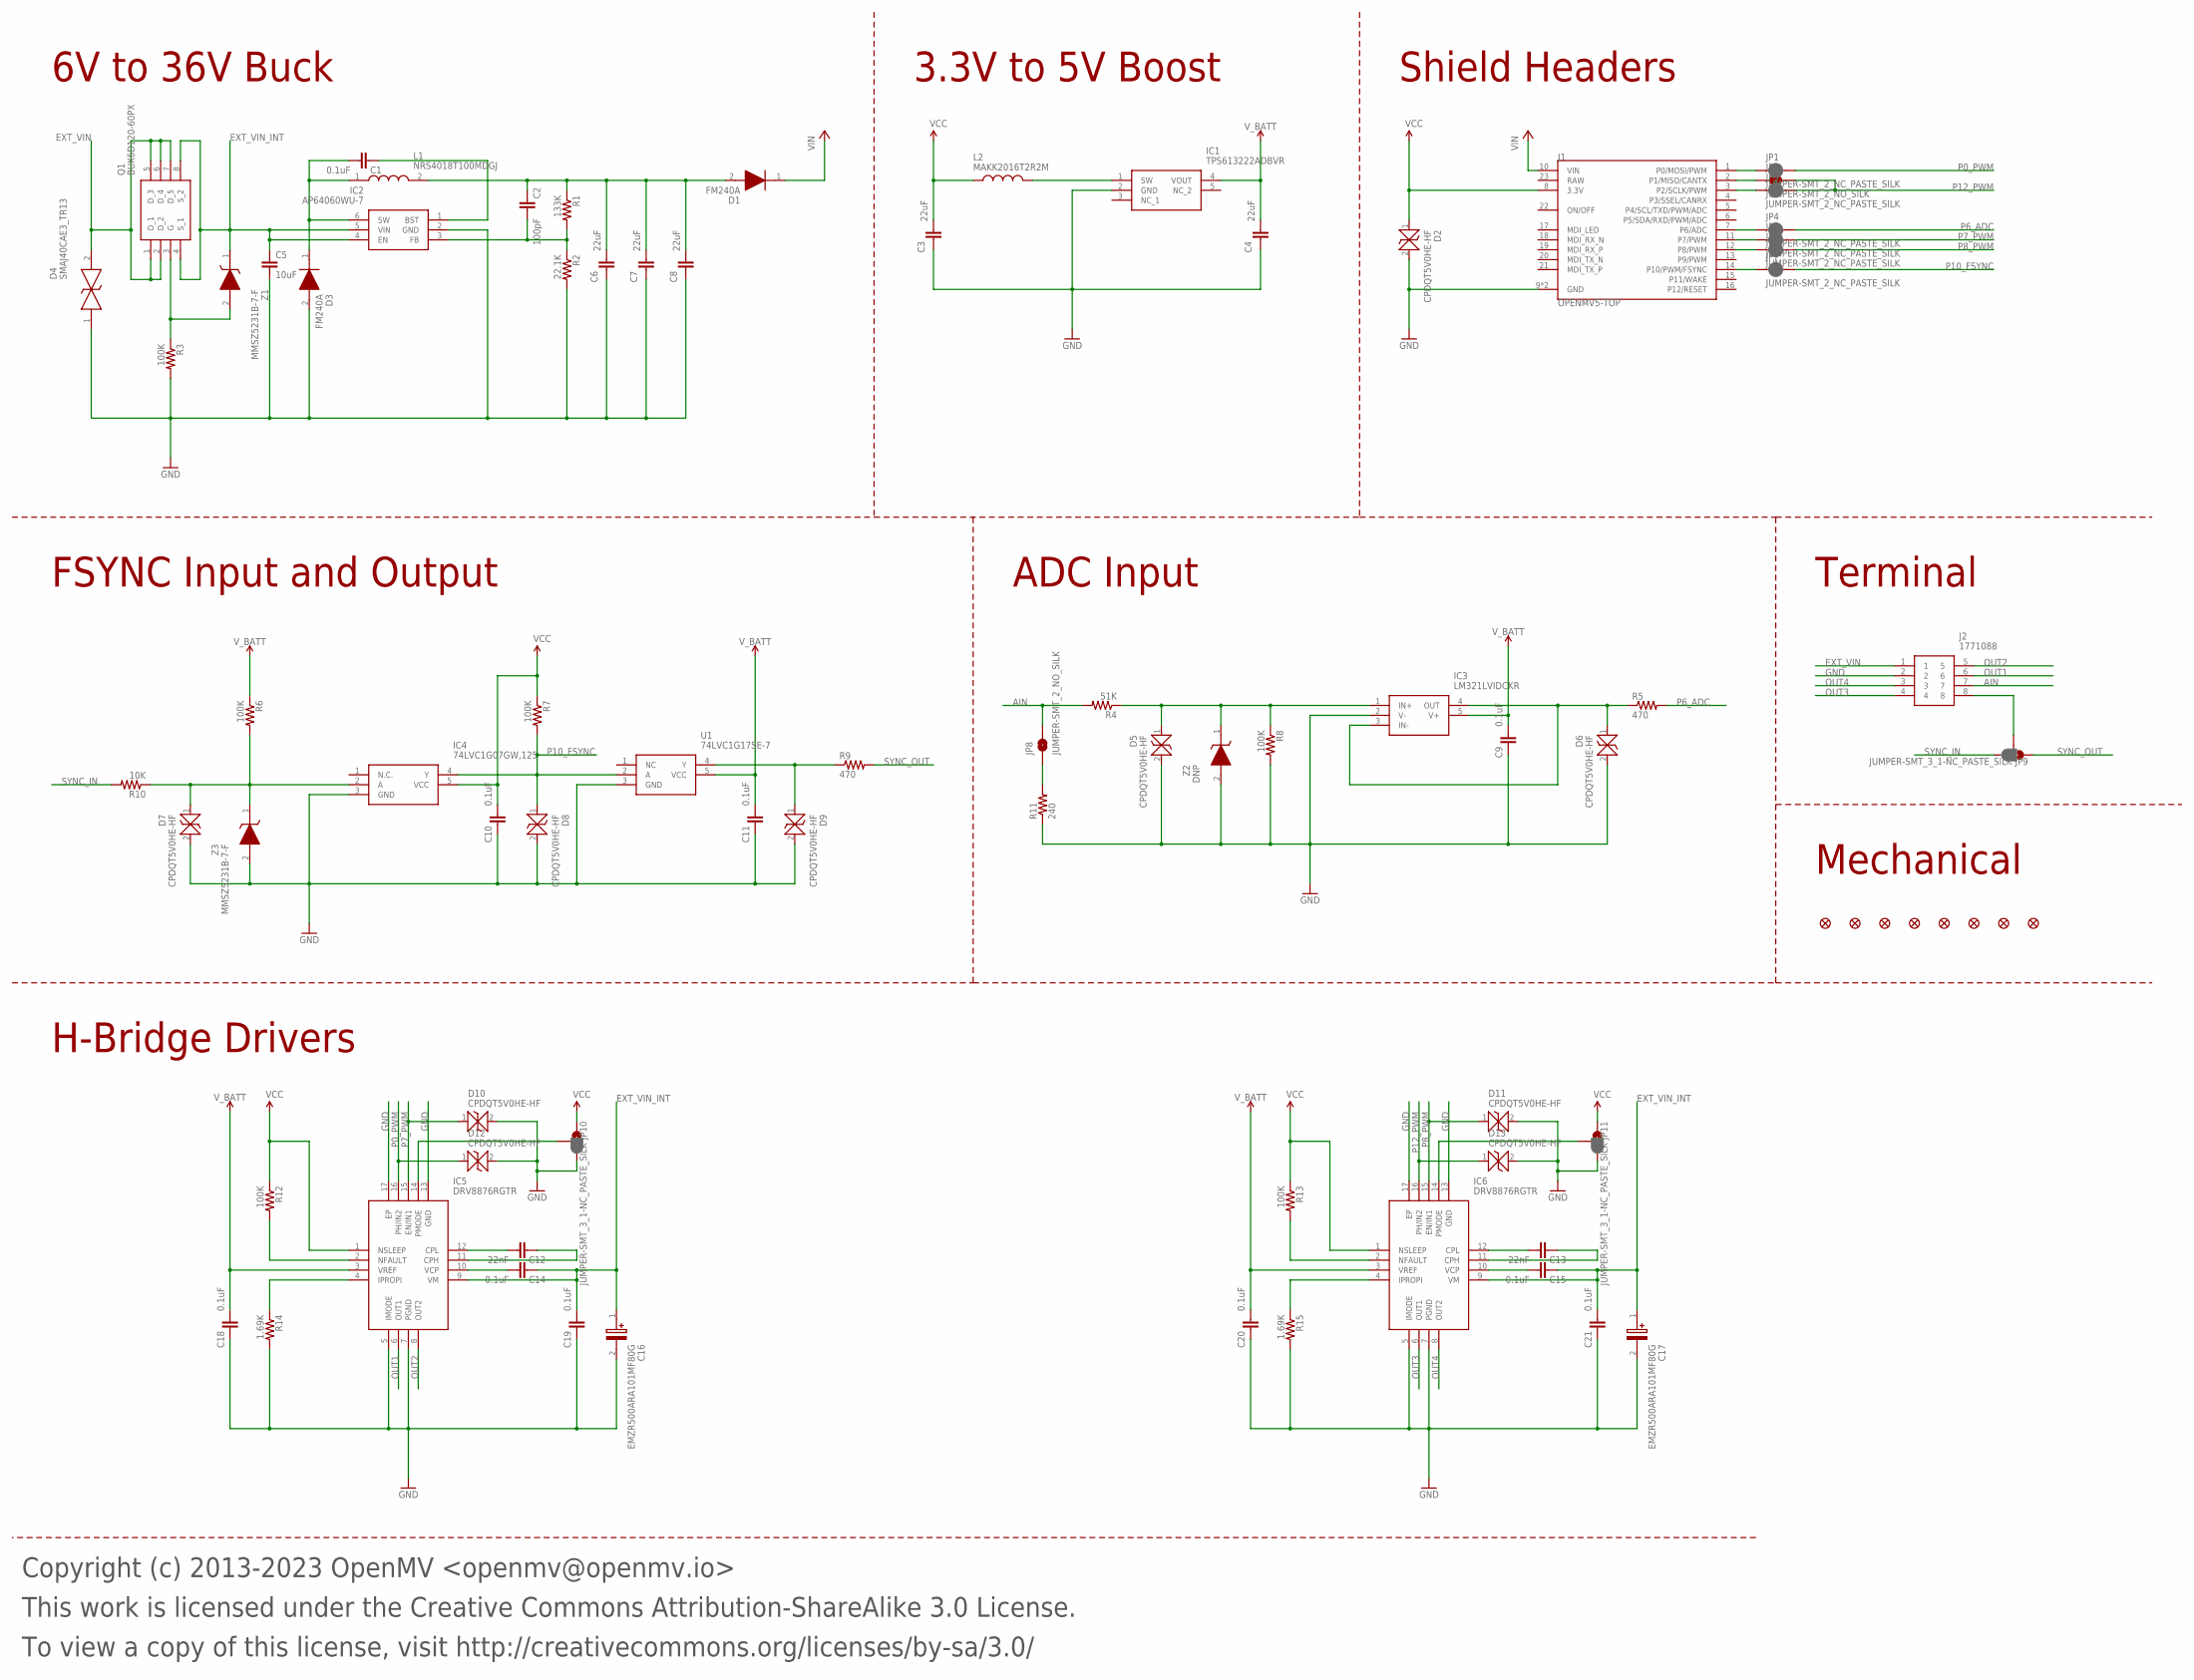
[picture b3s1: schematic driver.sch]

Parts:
C1, C9, C10, C11, C14, C15, C18, C19, C20, C21: 0.1uF; 0402-CAP; MPN GRM155R71H104KE14D
C2: 100pF; 0402-CAP; MPN CC0402JRNPO9BN101
C3, C4, C6, C7, C8: 22uF; 0805; MPN CL21A226MQQNNNE
C5: 10uF; C0805; MPN GRM21BR61H106KE43K
C12, C13: 22nF; 0402-CAP; MPN GRM155R71H223KA12D
C16, C17: EMZR500ARA101MF80G; CAPAE660X820N; MPN EMZR500ARA101MF80G
D1, D3: FM240A; DIOM5025X231N; MPN FM240A
D2, D5, D6, D7, D8, D9, D10, D11, D12, D13: CPDQT5V0HE-HF; CPDQT5V0HEHF; MPN CPDQT5V0HE-HF
D4: SMAJ40CAE3_TR13; SMAJ40CAE3TR13; MPN SMAJ40CAe3/TR13
FD1, FD2, FD3, FD4, FD5, FD6, FD7, FD8: FIDUCIAL1X2; FIDUCIAL-1X2
IC1: TPS613222ADBVR; SOT95P280X145-5N; MPN TPS613222ADBVR
IC2: AP64060WU-7; SOT95P280X100-6N; MPN AP64060WU-7
IC3: LM321LVIDCKR; SOT65P210X110-5N; MPN LM321LVIDCKR
IC4: 74LVC1G07GW,125; SOT65P212X110-5N; MPN 74LVC1G07GW,125
IC5, IC6: DRV8876RGTR; QFN50P300X300X100-17N; MPN DRV8876RGTR
J1: OPENMV5-TOP
J2: 1771088; MPN 1771088
JP1, JP3, JP4, JP5, JP6, JP7: JUMPER-SMT_2_NC_PASTE_SILK; SMT-JUMPER_2_NC_PASTE_SILK
JP2, JP8: JUMPER-SMT_2_NO_SILK; SMT-JUMPER_2_NO_SILK
JP9, JP10, JP11: JUMPER-SMT_3_1-NC_PASTE_SILK; SMT-JUMPER_3_1-NC_PASTE_SILK
L1: NRS4018T100MDGJ; MPN NRS4018T100MDGJ
L2: MAKK2016T2R2M; INDC2016X100N; MPN MAKK2016T2R2M
Q1: BUK6D120-60PX; BUK6D12060PX; MPN BUK6D120-60PX
R1: 133K; 0402-RES; MPN RC0402FR-07133KL
R2: 22.1K; 0402-RES; MPN CR0402-FX-2212GLF
R3, R6, R7, R8, R12, R13: 100K; 0402-RES; MPN AC0402FR-07100KL
R4: 51K; 0402-RES; MPN RC0402JR-0751KL
R5, R9: 470; R0603; MPN CR0603-FX-4700ELF
R10: 10K; 0402-RES; MPN AC0402FR-1310KL
R11: 240; R0603; MPN RK73B1JTTD241J
R14, R15: 1.69K; 0402-RES; MPN RC0402FR-07169RL
U1: 74LVC1G17SE-7; SOT65P210X110-5N; MPN 74LVC1G17SE-7
Z1, Z3: MMSZ5231B-7-F; SOD3716X145N; MPN MMSZ5231B-7-F
Z2: DNP; SOD2512X110N; MPN MM3Z3V6T1G

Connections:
AIN: J2.7, JP8.2, R4.2
AIN_INT: D5.1, IC3.1 (IN+), R4.1, R8.1, Z2.1 (K)
AIN_OUT: D6.1, IC3.3 (IN-), IC3.4 (OUT), R5.1
AIN_S: JP8.1, R11.2
CPH0: C12.1, IC5.11 (CPH)
CPH1: C13.1, IC6.11 (CPH)
CPL0: C12.2, IC5.12 (CPL)
CPL1: C13.2, IC6.12 (CPL)
EXT_VIN: D4.2, J2.1, Q1.1 (D_1), Q1.2 (D_2), Q1.5 (D_3), Q1.6 (D_4), Q1.7 (D_5)
EXT_VIN_BST: C1.1, IC2.1 (BST)
EXT_VIN_FB: C2.2, IC2.3 (FB), R1.2, R2.1
EXT_VIN_G: Q1.3 (G), R3.1, Z1.2 (A)
EXT_VIN_INT: C5.1, C14.1, C15.1, C16.1 (+), C17.1 (+), C19.2, C21.2, IC2.4 (EN), IC2.5 (VIN), IC5.9 (VM), IC6.9 (VM), Q1.4 (S_1), Q1.8 (S_2), Z1.1 (K)
EXT_VIN_OUT: C2.1, C6.2, C7.2, C8.2, D1.2 (A), L1.2, R1.1
EXT_VIN_SW: C1.2, D3.1 (K), IC2.6 (SW), L1.1
GND: C3.1, C4.1, C5.2, C6.1, C7.1, C8.1, C9.1, C10.1, C11.1, C16.2 (-), C17.2 (-), C18.1, C19.1, C20.1, C21.1, D2.2, D3.2 (A), D4.1, D5.2, D6.2, D7.2, D8.2, D9.2, D10.2, D11.2, D12.2, D13.2, IC1.2 (GND), IC2.2 (GND), IC3.2 (V-), IC4.3 (GND), IC5.5 (IMODE), IC5.7 (PGND), IC5.13 (GND), IC5.17 (EP), IC6.5 (IMODE), IC6.7 (PGND), IC6.13 (GND), IC6.17 (EP), J1.9 (GND), J1.24 (GND), J2.2, JP10.3, JP11.3, R2.2, R3.2, R8.2, R11.1, R14.2, R15.2, U1.3 (GND), Z2.2 (A), Z3.2 (A)
IPROPI0: IC5.4 (IPROPI), R14.1
IPROPI1: IC6.4 (IPROPI), R15.1
NFAULT0: IC5.2 (NFAULT), R12.2
NFAULT1: IC6.2 (NFAULT), R13.2
OUT1: IC5.6 (OUT1), J2.6
OUT2: IC5.8 (OUT2), J2.5
OUT3: IC6.6 (OUT1), J2.4
OUT4: IC6.8 (OUT2), J2.3
P0_PWM: D12.1, IC5.16 (PH/IN2), JP1.2
P0_PWM_INT: J1.1 (P0/MOSI/PWM), JP1.1
P1_PWM_INT: J1.2 (P1/MISO/CANTX), JP2.1
P2_PWM_INT: J1.3 (P2/SCLK/PWM), JP3.1
P6_ADC: JP4.2, R5.2
P6_ADC_INT: J1.7 (P6/ADC), JP4.1
P7_PWM: D10.1, IC5.15 (EN/IN1), JP5.2
P7_PWM_INT: J1.11 (P7/PWM), JP5.1
P8_PWM: D11.1, IC6.15 (EN/IN1), JP6.2
P8_PWM_INT: J1.12 (P8/PWM), JP6.1
P10_FSYNC: D8.1, IC4.4 (Y), JP7.2, R7.2, U1.2 (A)
P10_FSYNC_INT: J1.14 (P10/PWM/FSYNC), JP7.1
P12_PWM: D13.1, IC6.16 (PH/IN2), JP2.2, JP3.2
PMODE0: IC5.14 (PMODE), JP10.2
PMODE1: IC6.14 (PMODE), JP11.2
SW: IC1.1 (SW), L2.2
SYNC: J2.8, JP9.2
SYNC_IN: JP9.3, R10.2
SYNC_IN_INT: D7.1, IC4.2 (A), R6.2, R10.1, Z3.1 (K)
SYNC_OUT: JP9.1, R9.2
SYNC_OUT_INT: D9.1, R9.1, U1.4 (Y)
VCC: C3.2, C10.2, D2.1, IC4.5 (VCC), IC5.1 (NSLEEP), IC6.1 (NSLEEP), J1.8 (3.3V), JP10.1, JP11.1, L2.1, R7.1, R12.1, R13.1
VCP0: C14.2, IC5.10 (VCP)
VCP1: C15.2, IC6.10 (VCP)
VIN: D1.1 (K), J1.10 (VIN)
V_BATT: C4.2, C9.2, C11.2, C18.2, C20.2, IC1.4 (VOUT), IC3.5 (V+), IC5.3 (VREF), IC6.3 (VREF), R6.1, U1.5 (VCC)

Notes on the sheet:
Copyright (c) 2013-2023 OpenMV <openmv@openmv.io>
This work is licensed under the Creative Commons Attribution-ShareAlike 3.0 License.
To view a copy of this license, visit http://creativecommons.org/licenses/by-sa/3.0/
FSYNC Input and Output
Mechanical
Shield Headers
6V to 36V Buck
3.3V to 5V Boost
H-Bridge Drivers
Terminal
ADC Input
